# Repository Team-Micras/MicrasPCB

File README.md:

# MicrasPCB

The Micras micromouse PCBs, designed as code: circuits in [Zener](https://docs.pcb.new) (the
Diode `pcb` toolchain), layout in KiCad 10, and every check, fab output and review file built by
CI.

| Board | Status |
|---|---|
| `encoder`: AS5047U wheel encoder daughterboard, 2 layers, 0.79 mm | the previous revision's placement and routing, plus pull resistors on the sensor's SPI inputs; passes every check ([open items](boards/encoder/layout/README.md#open-items)) |
| `wall`: wall-sensor daughterboard (SFH 4550 over a TPS601A, upright, with the emitter's resistor and its AC-coupled selector, joined to the main board by a 2x3 1.27 mm header straddling its bottom edge), one per sensor, 2 layers, 0.79 mm, a paddle 16.0 mm high: 4.2 mm handle, 8.4 mm blade; JLCPCB fits the SMD parts on a 4-up panel, the sensor and header are hand-soldered | placed and routed, passes every check; the main board's wall joints W1-W4 take four ([open items](boards/wall/layout/README.md#open-items)) |
| `main`: STM32H725 controller, 4S power, DRV8874 wheel bridges with INA241 current sensing, fan driver, sensors, ESP32-C5 dual-band radio and debug probe, no USB receptacle (bare pads on the C5's native USB) ([research/next-revision](research/next-revision/README.md)), 4 layers, 1.04 mm, 91.15 x 50 mm | placed and routed for the six-pin wall slots, the fan ring, the ESP32 flashing pads and USB pads: every connection routed, passes every check ([open items](boards/main/layout/README.md#open-items)) |

The v1 main board and its HM-19 Bluetooth module, which plugged into the v1 board's USB-C port,
are at the tag `v1` (e34fb9a).

## How it fits together

```text
spec/<board>.toml ──────────────┐ outline, tab, spec-placed parts      ┌─> build/<board>/<board>_mech.json
                                 v                                      │   (MicrasHardware, micras-simulation)
boards/<board>/<board>.zen ──> pcb apply ──> micras-pcb sch ──> layout/<board>.kicad_sch
components/**/*.zen             (Zener)          ^                layout/<board>.kicad_pcb <─┘ placement + routing in KiCad
boards/<board>/schematic/*.toml ─────────────────┘ schematic placement
                                                     │
          make check: build · warnings · tests · sync · spec · sch · ERC · LVS · previous · DRC · DFM · pytest · parts
                                                     │
          make review: renders · schematic · layers · 3D · assembly · BOM · fab zip ──>  CI artifact
```

- **Zener owns the circuit.** Parts, nets, values, stackup and design rules are code, with
  datasheet evidence in docstrings and `pcb test` test benches for the datasheet requirements.
  `pcb apply` writes the KiCad schematic and syncs the netlist into the layout, keeping hand
  placement and routing (sync is idempotent: a regeneration of an unchanged design is
  byte-identical).
- **`boards/<board>/schematic/` owns how the schematic is drawn.** `pcb apply` writes each sheet
  afresh; `micras-pcb sch` then places it from one file per sheet: where each part goes and how it
  turns, which pins are wired together, the titled frame of each function block, the paper size
  and the order of each module's sheet pins. It redraws every connection with the labels and
  power symbols pcb chose and fails unless KiCad's netlist of the placed schematic equals pcb's,
  so the drawing can never change the circuit. A part without an entry is drafted from the
  netlist by the same rules a person follows (blocks by connectivity, decoupling at the supply
  pin, pulls at their pins, repeated blocks alike, the smallest paper), steered by an optional
  `SCHEMATIC_HINTS` dict in the Zener module that pcb ignores; `micras-pcb sch --draft` writes the
  drafts into the file to adopt and adjust. The `micras-pcb` skill has the file format, the rules
  and the hints.
- **`spec/` owns the mechanics.** `micras-pcb mech` writes the origin and the locked position of
  mechanically critical parts (the encoder's sensor and tab, the wall board's sensor and header,
  the main board's screw holes, battery switch, ESP32 module and wall sensors) into the
  `.kicad_pcb`, and exports the board for the other repos. The main board's and the wall board's
  Edge.Cuts outlines are the spec's (`micras-pcb mech` draws them: the main board's nose, wheel
  notches, encoder slots, fan hole, antenna and switch notches; the wall board's bottom edge,
  sides and corners), and so is the main board's silkscreen of the fan ring and the drive
  blocks' outlines; the encoder's is layout
  geometry (it keeps its previous revision's), and the spec checks its interface features (tab,
  shoulder, tapers and extents). CI fails if the layout drifts.
- **KiCad owns placement and routing**, which stay human-led.
- **`parts/jlc.toml` owns sourcing**: MPN to LCSC number, basic/extended, placement rotation.
- **The order options** come from where each is decided: finish and colours from the Zener
  stackup, the via class and the assembly service from `spec/<board>.toml` `[pcb]` (a test holds
  the via class to the layout's smallest via), and a board under JLCPCB's 10 x 10 mm assembly
  minimum is ordered as the panel its spec's `[panel]` describes (KiKit, `make fab`). Every board is
  leaded HASL. JLCPCB prints no paste on the parts the team solders itself (`assembly = "hand"`):
  their paste goes to a separate stencil file (`micras-pcb` skill, JLCPCB outputs).

### Why Zener and KiCad

- **KiCad 10 is the contract between tools.** `kicad-cli` runs ERC, DRC and every export
  headless, MicrasHardware imports the board through KiCad's STEP, and JLCPCB's assembly flow is
  built around KiCad. The committed KiCad project is a complete design on its own: without Zener,
  the boards continue in plain KiCad and only the schematic stage changes.
- **Zener writes the schematic**, the part of KiCad that is weakest as code: KiCad 10 has no
  headless schematic API, and its verbose files are a poor target for language models. Zener emits
  a real KiCad schematic to review, syncs the netlist into the layout without touching hand
  placement and routing, type-checks power nets, runs datasheet test benches, and is built to be
  written by agents (its skills are in `.claude/skills/`).
- **`tools/micras_pcb` covers the rest**: the spec-driven outline and mech export, LVS, the rule
  checks, and the JLCPCB package with its rotation offsets.

### Known limits

- **Zener is pre-1.0 and changes fast**; commands get renamed or removed between releases. The
  toolchain is pinned in `versions.env` and bumped in its own PR, where CI shows what regenerates.
- **Zener has no LCSC picker, and its JLC placement export applies no rotation corrections.**
  `parts/jlc.toml` carries the LCSC number and a per-part rotation offset, and `make fab` builds
  the JLCPCB BOM and CPL from it. JLCPCB's placement preview is the final word on each part's
  rotation (`rotation_verified`).
- **Zener labels the nets between module sheets twice**: the main board's schematic has one
  sheet per Zener module (`Project(..., layout = False)`), and pcb 0.4.81 puts
  a global label beside each sheet pin and hierarchical label
  ([diodeinc/pcb#1520](https://github.com/diodeinc/pcb/issues/1520)), so KiCad's ERC warns
  `same_local_global_label` and `multiple_net_names` on those nets. The placement keeps the global
  label at the pin and draws the hierarchical one in the sheet's ports column, wired to a copy of
  the global one (`micras-pcb sch`). Each board's
  `erc.toml` accepts these two warnings with that reason, and only them; they go away with a pcb
  release that includes [diodeinc/pcb#1522](https://github.com/diodeinc/pcb/pull/1522)
  ([known faults](boards/main/layout/README.md#known-faults)).
- **KiCad 10 has no headless layout API**: the IPC API needs a running KiCad, and the SWIG
  `pcbnew` module is deprecated and goes away in KiCad 11. The tools use `kicad-cli` and edit the
  `.kicad_pcb` s-expressions directly (`tools/micras_pcb/sexpr.py`).
- **Git cannot merge a `.kicad_pcb` safely** (KiCad 10 has no merge driver): one person edits a
  board's layout at a time.
- **Footprints from EasyEDA/LCSC have documented errors** (reversed polarity, wrong pin numbering,
  mismatched pads). Use KiCad library footprints where they exist, and check every footprint
  against the datasheet land pattern, its 3D model and JLCPCB's preview.
- **JLCPCB has no ordering API open to small teams**: order by uploading `build/<board>/fab/` by
  hand.

## Setup (Linux / WSL2)

```sh
./ci/install-kicad.sh                                                                # KiCad 10 from the PPA, see versions.env
curl -fsSL https://raw.githubusercontent.com/diodeinc/pcb/main/install.sh | bash      # Zener toolchain launcher
make setup                                                                            # uv env + pinned pcb toolchain + KiKit
```

Optional: the [Zener VS Code extension](https://docs.pcb.new/pages/vscode) shows a live
schematic preview of `.zen` files.

## Everyday commands

```sh
make gen        # regenerate KiCad files from the sources (run after every source change)
make check      # every gate CI runs, with a pass/FAIL summary
make review     # build/<board>/review and fab: schematic PDF, layer SVGs, renders, GLB/STEP, fab package,
                #   and build/main/review/assembly.*: the main board with its wall and encoder boards in place
make fab        # build/<board>/fab: JLCPCB gerbers zip (no paste on hand-soldered parts), BOM, CPL, order options
                #   (the wall board's as a 4-up panel) and the team's stencil for the hand-soldered parts
pcb open boards/encoder/encoder.zen     # open the layout in KiCad
make parts-online   # JLCPCB stock and basic/extended status (run before ordering)
make quote          # JLCPCB's bare-board price with each board's finish, colours and via class
```

`make check` runs every gate below, even after one fails, then prints a pass/FAIL line per gate
and fails if any gate failed.

| Gate | Tool | Catches |
|---|---|---|
| build | `pcb` | Zener errors, electrical type checks (power pins), formatting, dependency drift |
| warnings | `pcb build -D warnings` | a build warning: a net outside a part's declared operating range, a capacitor rated below its net |
| test | `pcb test` | datasheet requirements: per component (`components/**/test/`) and per board (`boards/<board>/test/`: application circuits, values computed with the datasheet equations) |
| layout-check | `pcb layout --check`, `micras-pcb rules/mech --check` | layout no longer matches the netlist, rules or spec drift |
| sch | `micras-pcb sch --check` | a placement entry, wire or hint naming what its sheet does not have, a sheet symbol too small for its pins, overlaps or items off the page, a placed sheet out of date with the sources; prints how many parts each sheet drafts |
| ERC | `kicad-cli sch erc` | schematic electrical rules; `boards/<board>/erc.toml` names the nets supplied from off the board (the PWR_FLAG role) and the warnings a board accepts, rule by rule with the reason |
| LVS | `micras-pcb lvs` | schematic and PCB connect different pads |
| previous | `micras-pcb previous compare <board>` | a replicated board (the encoder) connects or names anything differently from its previous revision, except the changes in `boards/<board>/changes.toml` |
| DRC | `kicad-cli pcb drc` + `rules/jlcpcb.kicad_dru` | JLCPCB clearances (copper, SMD pad to pad, hole to track), widths, drills, edge distances |
| DFM | `pcb dfm` + `rules/jlcpcb-pdk.toml` | geometry-level manufacturability (Diode's sourced JLCPCB PDK) |
| pytest | `pytest` | board contracts (encoder joint, firmware pin map), the assembly (each wall and encoder board standing where the specs put it, its pads on its joint's, clear of the main board and its parts), the fab package (every assembled board or its panel at least 10 x 10 mm, the panel's outlines, tabs and CPL, each board's via class), power tree, every schematic item on its sheet's page, no overlapping texts, bodies or wires on a sheet, every board's schematic drafted whole from its Zener source (pcb's netlist, nothing overlapping), decoupling at the pin, encoder slot fit, routing style (every track straight at a multiple of 45 degrees, no arcs, no acute corners), courtyards, paste, 3D models, part data |
| lint | `ruff` | Python lint and format |
| parts | `micras-pcb parts` | a part without an LCSC mapping |

Every board passes every gate once laid out. A schematic-only board (its root declares `Project(layout = False)`, so it has no
`.kicad_pcb`) passes the schematic gates, and LVS, DRC, DFM, the layout tests and the gerber, CPL
and 3D outputs skip it with that reason; `make fab` writes
its BOM alone. The main board's README ([known faults](boards/main/layout/README.md#known-faults))
gives the root cause of each warning that remains.

## CI

- `.github/workflows/ci.yml`: on every push and PR, installs the pinned KiCad and Zener,
  checks that `make gen` changes nothing, runs `make check`, builds the review outputs and fab package
  (uploaded as the run's artifact).
- GitHub Actions, the Python dev tools (`uv.lock`), KiCad and Zener (`versions.env`) are bumped
  by hand; a KiCad or Zener bump can change the generated files.
- JLCPCB stock is not checked in CI (it changes daily and the API is undocumented): run
  `make parts-online` before ordering.

To look at a board, download the run's artifact, or open the project in KiCad
(`pcb open boards/<board>/<board>.zen`). The boards are also viewed online in a self-hosted
[KiCad Prism](https://github.com/krishna-swaroop/KiCAD-Prism), which takes each board's layout
folder as a project and shows the board's README from it (`boards/<board>/layout/README.md`).
Each layout folder's `.prism.json` names the root schematic and the board, so Prism does not take
the first sheet in the folder (main's `DRIVERS.kicad_sch`) as the root and drop it from the viewer.
Prism shows one board at a time; the robot's boards together are in the run's artifact:
`build/main/review/assembly.glb` and `assembly.step` (the main board with the four wall boards and
both encoder boards standing in their joints, origin at the robot's) and the renders
`assembly-iso-left.png`, `assembly-iso-right.png` (from the front-left and front-right) and
`assembly-top.png`. `micras-pcb assembly` places each daughterboard from the specs on a build copy
of the main board, as a 3D model on its joint footprint, and fails if KiCad's export puts it
anywhere else.

## Working with Claude Code

`CLAUDE.md` holds the agent rules. `.claude/settings.json` adds two hooks: one rebuilds any
`.zen` file the agent edits and feeds errors back immediately; the other blocks text edits to
generated or KiCad-owned files. `.claude/skills/` holds the `micras-pcb` workflow skill (parts,
JLCPCB outputs, KiCad scripting, review gates) and Diode's Zener skills (language, component
librarian, SPICE). Agents write code and deterministic tools grade it; people own footprint and
pin-1 checks, placement and routing, and the fab order.

## Repository

```text
boards/<board>/        <board>.zen, pcb.toml, layout/ (KiCad project: .kicad_pcb is KiCad-owned, README.md is
                       the board's description, .prism.json the root files for KiCad Prism, the rest generated)
boards/<board>/schematic/  one placement file per schematic sheet (micras-pcb sch): parts, wires, frames, paper;
                       drafted entries marked auto = true
boards/<board>/previous/  snapshot of the board's previous revision (board.json) for the connectivity comparison,
                       and the script that builds its layout from that revision (transfer_layout.py): the encoder
boards/main/layout/*.py  the main board's placement, routing and silkscreen scripts (place.py, route.py, silk.py;
                       its layout README says what each does) and their 45-degree grid router (router.py)
boards/main/firmware.toml  the firmware's pin map and drive settings (from MicrasFirmware), tested against the board
boards/main/firmware_changes.toml  the firmware changes the board needs, applied on top of firmware.toml in the tests
boards/<board>/test/   Zener test benches of the board's circuit
components/<mfr>/<P>/  reusable Zener packages: symbol, footprint (STEP embedded), .zen, test bench, README
spec/                  mechanical single source of truth per board; main_chassis.json, the chassis's shadow over the
                       main board from MicrasHardware's model (tools/chassis_shadow.py, run in that repo's environment)
parts/jlc.toml         MPN -> LCSC mapping
rules/                 JLCPCB KiCad DRC rules, DFM PDK, KiCad rule severities
tools/micras_pcb/      Python glue: mech, lvs, checks, jlc, panel, order, outputs, assembly, previous, firmware, layout,
                       schematic placement and drafts (`uv run micras-pcb --help`)
tests/                 pytest design tests
research/next-revision/ the main board's design research (entered as boards/main) and its calculation scripts
ci/                    KiCad, toolchain and KiKit install, for CI and local setup
versions.env           pinned KiCad, Zener, Freerouting and KiKit versions
```

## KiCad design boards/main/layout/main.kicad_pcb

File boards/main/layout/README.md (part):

# Main board

The Micras main board: the STM32H725RGV6 controller, a 4S
battery input with its fuse, VSYS behind a Schottky, separate digital and analog 3.3 V rails, two
DRV8874 wheel bridges with in-line INA241 current sensing, the STSPIN958 fan driver, the IMU,
the joints for four wall-sensor boards (boards/wall) on a shared emitter current sink, the slots
for the two encoder boards, the
ESP32-C5 dual-band radio, debug probe and data link with its flashing pads and bare USB pads, and
the user interface. The board has no USB receptacle: bare pads J3 take a USB cable's data pair and
ground, soldered once, on the ESP32-C5's native USB; a programmer's 5 V pin on the flashing pads or
the SWD pads (5V_IN) powers it for flashing without the pack.

The design is [research/next-revision/README.md](../../../research/next-revision/README.md): its
design basis (maxon DCX 10 L 4.5 V motors on a 4S pack, no boost; no USB receptacle; no 5 V rail), the options it recommends, and its connection lists A.1-A.6. The blocks it keeps are
the v1 main board's (MicrasPCB e34fb9a, `boards/main`), with their designators; new parts continue each series (C80-C114, D14-D15, D17,
IC8-IC9, J2-J3, L4-L6, Q9, R58-R97, U8-U13), and the designators of removed parts are not reused.

The board is 91.15 x 50 mm (x 47.6 to -43.55 in the robot frame), 4 layers, 1.04 mm, every part on the
top side. Its mechanics are [`spec/main.toml`](../../../spec/main.toml): the outline, the screw
holes, the encoder slots, the wall joints, the fan hole and its low-part ring, the antenna and switch
notches, the parts that mate with the robot or the outline (IC1 among them) and the zones the chassis
takes over the board (see [Layout](#layout)). The robot fills the smallest turning circle the parts
allow, 49.46 mm round the axle: the nose (its front edge 18.2 mm wide between 4 mm corner arcs, with long chamfers meeting the sides in 4 mm shoulder arcs) holds the diagonal
wall sensors at the front, IC1 behind them turned 45 deg and partly over the fan ring (spec `[ic1]`:
x 32.35, its courtyard 0.73 mm from the fan hole and 1.82 mm from the diagonal joints' courtyards, for its
decoupling; the ring's silk breaks at its pads), and the frontal sensors beside it at y +-19.8; the parts ahead
of the fan hole's centre keep about the committed board's density (39.1 %, 34.5 % on the committed
outline). The rear edge sits where U13's antenna corner reaches the same circle; the module alone
would allow a rear edge up to -41.3 (its courtyard behind the right drive block's rear screw boss).
The front-row LEDs (D1, D2, D4/R4, D5/R5) move back 5.9 mm with the front edge, in the same
arrangement (owner, 2026-11-03).

## Files

The board files are in `boards/main/` (this README sits in its `layout/` folder).

| File | Sheet instance | Contents |
|---|---|---|
| [`main.zen`](../main.zen) | root | IC1 (STM32H725RGV6) and its supply network (C1-C17, L1, R67), the ST-Link pads SWD1 (NRST on pad 1, 5V_IN on pad 5), M2 screw holes H1-H4 |
| [`Regulators.zen`](../Regulators.zen) | `REGULATORS` | J1 battery connector with its fuse F1 and TVS D15, battery switch SW4/Q6, battery measurement R44/R45, VSYS diodes D14 (from VBAT) and D17 (from 5V_IN), 3V3_D buck IC7, 3V3_A LDO U8 |
| [`Drivers.zen`](../Drivers.zen) | `DRIVERS` | IC8/IC9 (DRV8874) bridges for M2/M1 with their 10 mOhm shunts R65/R75 and 47 uH chokes L4/L5, IC6 (STSPIN958) fan driver for M3 with its shunt R31 and 4.7 uH choke L6 |
| [`Sensors.zen`](../Sensors.zen) | `SENSORS` | IC2 (LSM6DSV) IMU, U10/U11 (INA241A2) current amplifiers, wall joints W1-W4 (the wall boards' 2x3 joints: receiver output, GND, 3V3_A, 3V3_D, sink, PWM) with the receivers' 1 kOhm loads R14/R18/R22/R26, the emitter current sink U12/Q9/R83 with its DAC set-point, encoder slots EC1/EC2 |
| [`Peripherals.zen`](../Peripherals.zen) | `PERIPHERALS` | SW1 DIP switch, SW2/SW3 buttons, R42 BOOT0 pull-down, BZ1 buzzer, D1/D2 (CT-1515UGRBC) status LEDs, D4/D5 LEDs |
| [`Esp.zen`](../Esp.zen) | `ESP` | U13 (ESP32-C5-MINI-1-N4) with its decoupling, EN RC, GPIO28 pull-up, flashing pads J2 (`components/micras/EspProgPads`, 5V_IN on pad 2), the USB pads J3 (`components/micras/UsbPads`, GPIO13 D-, GPIO14 D+), and the links to the MCU with their series resistors R86, R88, R95, R96 and the ESP_CSn pull-up R97 |
| [`passives.zen`](../passives.zen) | | value, package, rating and part number of every resistor, ceramic capacitor and LED line |
| [`schematic/`](../schematic) | | how each sheet is drawn (`micras-pcb sch`): the root with IC1, its supply domains, the SWD header and the module sheets, and one file per module sheet, each block in a titled frame |
| [`erc.toml`](../erc.toml) | | nets supplied from off the board (BAT_P, GND, GND_BAT, 5V_IN) or through a passive part (VBAT, VSYS, 3V3_D, the LDO input, VDDA), the PWR_FLAG role for ERC; the two ERC warnings the module sheets leave until a pcb release includes [diodeinc/pcb#1522](https://github.com/diodeinc/pcb/pull/1522) (see [Known faults](#known-faults)) |
| [`firmware_changes.toml`](../firmware_changes.toml) | | the firmware changes this board needs against the v1 firmware (see [Firmware changes](#firmware-changes)) |
| [`test/`](../test) | | `pcb test` benches: MCU and ESP links, power, drivers, peripherals |
| [`layout/`](.) | | this folder: the KiCad project; `main.kicad_sch` is the root sheet, with one sheet per module (`REGULATORS.kicad_sch`, ...); the `.kicad_pcb` holds placement and routing; `place.py` places every part, `route.py` pours the planes and routes the board and `silk.py` places the reference designators (see [Layout](#layout)) |
| [`spec/main.toml`](../../../spec/main.toml) | | mechanical interface: thickness, axle origin, outline, screw holes, encoder slots, wall joints, fan hole and fan ring, wheel, antenna and switch notches, the ESP32 module's, battery switch's and wall joints' positions, the chassis zones, the silkscreen it draws (fan ring, drive blocks); the via-in-pad order option |

Each module is its own sheet of the KiCad schematic (`Project(..., layout=False)` in its `.zen`),
its signal ports named after the nets they carry where those names are identifiers, as on the
v1 main board. `SENSORS` takes the shared SPI bus once (`SPI_SCK`, `SPI_MISO`, `SPI_MOSI`) with
each device's chip select, not one `Spi` port per device, so it has 26 sheet pins instead of 32:
pcb 0.4.81 places the sheet symbols on the root one by one in the order of their names, each as
near the page centre as the earlier ones leave room, by their boxes alone, and the 32-pin symbol
fits only against the page's left edge, where its pin labels run past the page. At 26 pins it sits
right of `ESP`, and `tests/test_schematic.py` checks that every label stays on its page. Each sheet's docstring describes its circuit with the datasheet figure, table or
equation behind each value; [`tests/test_main.py`](../../../tests/test_main.py) checks the power tree, the analog
rail, the decoupling and the firmware contract on the generated netlist.

## Power

```text
4S LiPo 12.0-16.8 V (17.4 V HV) ─ J1 ─ BAT_P ─ F1 12 A fuse ─ VBAT (D15 SMAJ18A to GND_BAT)
   pack - ─ GND_BAT ─ Q6 HSBB3072 (SW4, slew-limited) ─ GND
VBAT ─┬─ IC8/IC9 DRV8874 VM, IC6 STSPIN958 VS
      ├─ R44/R45 20k/2k ─ PC5 (Battery_Voltage, ratio 11.0)
      └─ D14 B5819W ─ VSYS 11.4-17.4 V (3.8-5.0 V on 5V_IN alone)
5V_IN (a programmer's 5 V pin: J2 pad 2, SWD1 pad 5) ─ D17 B5819W ─ VSYS
      VSYS ─┬─ IC7 L6981C33 ─ 3V3_D: MCU VDD, ESP32, IMU, encoders, LEDs, emitters
            └─ R58 22 Ω + C80 10 µF ─ U8 ADP7142 3.3 V (EN = 3V3_D) ─ 3V3_A: VDDA (R67 0 Ω),
                  INA241 VS/REF1, phototransistor collectors, emitter-sink op-amp and its bias
```

- **VSYS** is VBAT behind D14, or 5V_IN behind D17, and feeds only the two regulators. D14 keeps
  5V_IN off VBAT, the bridges' bulk and the pack; D17 keeps the pack off the programmer.
- **No USB supply input**: every rail comes from J1 but for flashing. 5V_IN takes a USB-serial
  adapter's, a clone ST-Link's or the J3 USB cable's 5 V wire (never a 3.3 V one) on J2 pad 2 or SWD1 pad 5 and runs the 3V3 rails
  without the pack: 0.19-0.25 A while flashing, VSYS 3.8 V or more, where the buck still
  regulates; the bridges and the fan stay unpowered and VBAT reads near 0 V (Regulators.zen,
  VSYS). On the bench, a current-limited supply at 12-16.8 V goes into J1 (a lead with the pack's
  JST PA plug) with SW4 on; with the motors and the fan disabled, set the limit just above what
  the 3V3 rails draw.
- **3V3_D**: the L6981C33 buck, as on the v1 main board, now from VSYS; every capacitor on 3V3_D,
  the ESP32's 22 uF included, stays inside its 30.5-145 uF compensation window.
- **3V3_A**: the ADP7142ACPZN3.3 LDO from VSYS through 22 Ohm + 10 uF 1210, its EN on 3V3_D so VDDA
  never leads VDD; about 10 mA typical, 23 mA worst case, 0.32 W at the HV pack's top.
- **No 5 V rail** (5V_IN is a programming input, not a rail).
- **Battery voltage**: R44/R45 20k/2k into PC5 with C59 100 nF: 1.58 V at 17.4 V and 2.20 V at
  D15's 24.2 V clamp, under PC5's 4.0 V absolute maximum (a ratio of 6 reaches 4.03-4.10 V there).
- **Fuse**: F1, Littelfuse 0501012.WR1 (12 A fast-acting, 32 VDC, 150 A interrupting, 3.2 mOhm;
  a 1206 under the chassis's 1.5 mm zone), carries the whole battery current from J1 to VBAT: a
  short on the board opens it. It carries the 4 A rms budget with 2x margin at 75 C (8.2 A) and
  holds the 10.1 A summed peak limits at 75 C (10.2 A); it clears a 40 A partial fault in about
  6 s (the 20 A row: about 25 s). Turning the board on is under 0.01 A2s against its 20.3 A2s.
- **Battery switch**: Q6 as on the v1 main board, its gate fed from VBAT through SW4; C58 100 nF
  gate-source and C114 1 nF gate-drain keep it off when the pack is plugged in (the board then
  sees no edge), and slew VBAT at about 0.06 V/us when SW4 closes, under the STSPIN958's
  0.5 V/us. SW4 is the SK-12D29-G060
  (DC 24 V, the v1 main board's switch body with a 6.0 mm lever, its own footprint). The connector
  keys the polarity; a reversed pack forward-biases D15 through F1, which opens.
- **TVS**: D15 (SMAJ18A, 18 V standoff, 20-22.1 V breakdown) behind F1, VBAT to GND_BAT, so a
  TVS that fails short opens the fuse. With the
  pack pulled while the bridges brake, it holds VBAT near 21-23 V through Q6's channel (SW4 on) or
  its body diode (SW4 off), at most 24.2 V, below every rating on VBAT and VSYS (50 V MLCCs,
  Q6's 30 V, the DRV8874's 40 V).
- **No electrolytics**: VBAT carries only ceramics, every 10 uF a 50 V X7R 1210 (61 uF effective
  at 16.8 V); the research's
  [VBAT capacitance](../../../research/next-revision/README.md#power-tree) compares the options and
  quantifies the VBAT overvoltage cases.

## Drivetrain and current sensing

- **Bridges**: one DRV8874PWPR per motor, PH/EN mode (PMODE = GND), PWM on EN and direction on
  PH (right PA10/PB6, left PC6/PA12), IMODE = GND (fixed off-time, automatic retry), ITRIP 2.97 A
  from RIPROPI 2.0 kOhm and VREF 2.67 V (4.7k/20k from 3V3_D). nSLEEP of both on Motors_Enable
  (PB7) with R49 100 kOhm to GND; nFAULT of both wire-ORed on Motors_nFault (PD2) with R60
  10 kOhm to 3V3_D. Per bridge: 100 nF + 4 x 10 uF 50 V X7R 1210 on VM, 100 nF VCP, 22 nF
  CPH-CPL.
- **Motor path**: OUT1 -> 10 mOhm WSK2512 4-terminal shunt -> 47 uH MTQH707050S470M choke -> motor
  connector; OUT2 -> connector.
- **Current**: INA241A2 (gain 20) on each shunt, VS and REF1 on 3V3_A, REF2 on GND: 0.2 V/A
  around VDDA / 2, +7.25 / -8.15 A at 3V3_A 3.3 V, into PA6 (left, a fast ADC channel) and PC1 (right)
  through 150 Ohm (R78/R79, R_iso), with 1 nF X7R on the ADC line (C102 3.5 mm from PC1, C105
  1.9 mm from PA6, 2 mm of track from the pin); the firmware samples them
  for at least 0.7 us, so the ADC's kickback from a wall-sensor conversion settles below 1 mA.

## Fan

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
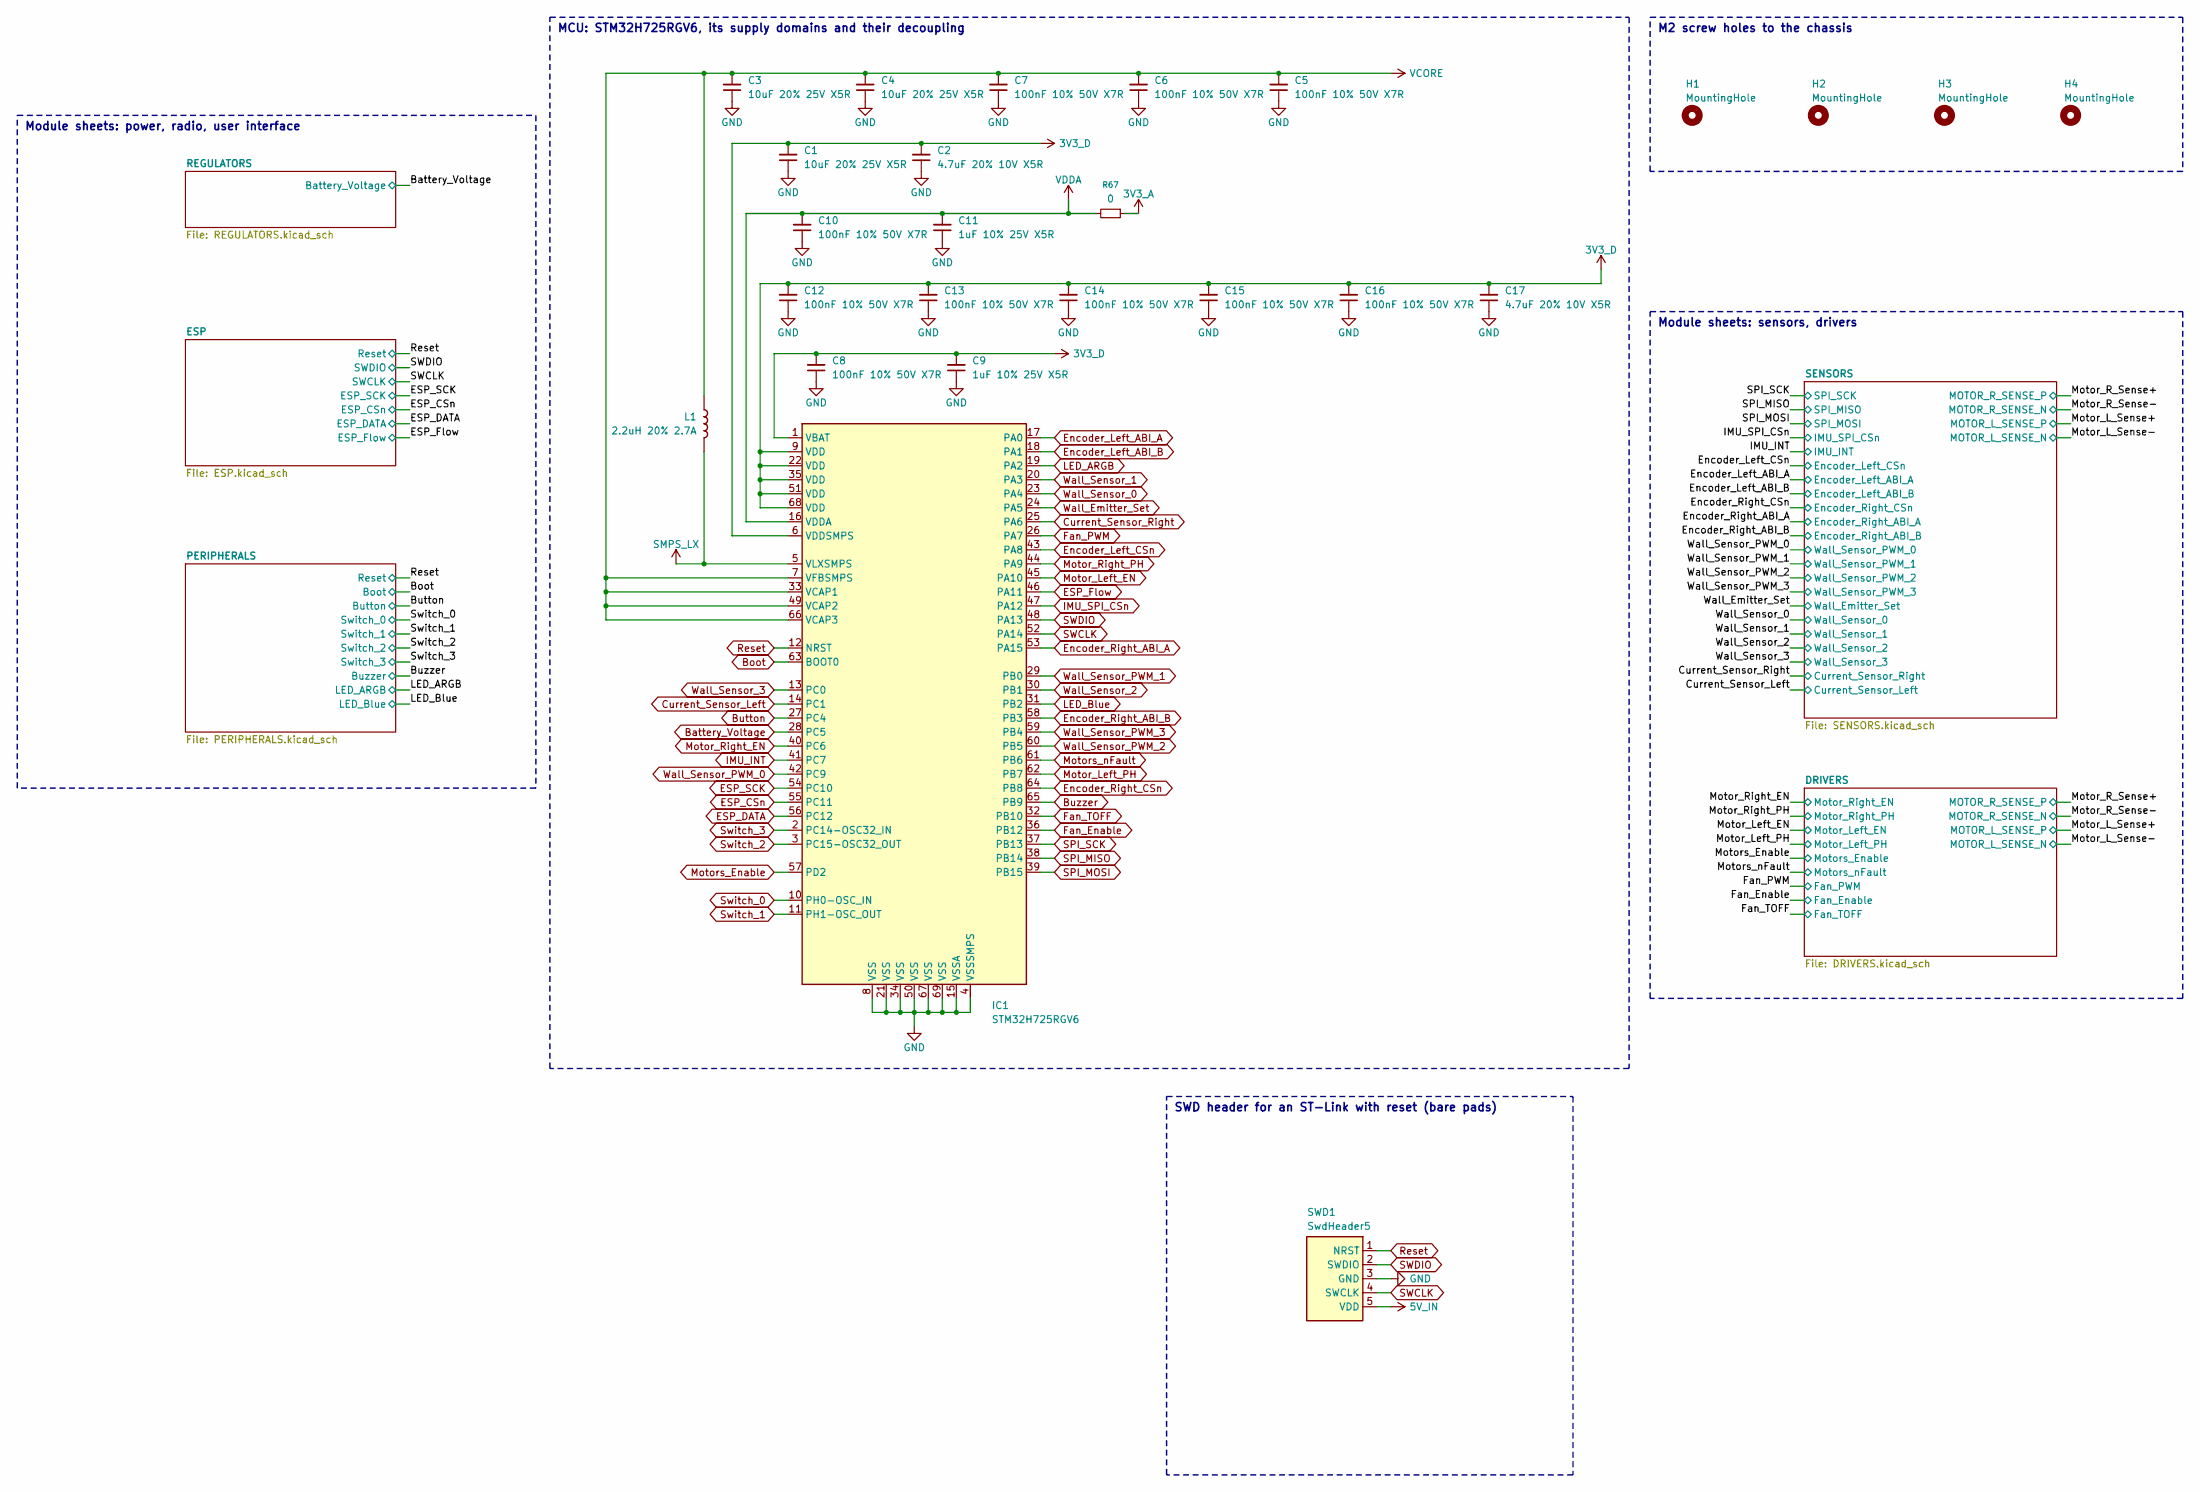
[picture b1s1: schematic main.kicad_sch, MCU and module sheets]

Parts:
C1, C3, C4: 10uF 20% 25V X5R; C_0603_1608Metric
C2, C17: 4.7uF 20% 10V X5R; C_0402_1005Metric
C5, C6, C7, C8, C10, C12, C13, C14, C15, C16: 100nF 10% 50V X7R; C_0402_1005Metric
C9, C11: 1uF 10% 25V X5R; C_0402_1005Metric
H1, H2, H3, H4: MountingHole; MountingHole_2.4mm_NPTH
IC1: STM32H725RGV6; QFN-68-1EP_8x8mm_P0.4mm_EP6.5x6.5mm_SplitPaste
L1: 2.2uH 20% 2.7A; IND-SMD_L2.0-W1.6-B
R67: 0; R_0402_1005Metric
SWD1: SwdHeader5; PinHeader_1x05_P1.27mm_Vertical

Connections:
3V3_A: R67.1; also elsewhere on the board
3V3_D: C1.2, C2.2, C8.2, C9.2, C12.2, C13.2, C14.2, C15.2, C16.2, C17.2, IC1.1 (VBAT), IC1.6 (VDDSMPS), IC1.9 (VDD), IC1.22 (VDD), IC1.35 (VDD), IC1.51 (VDD), IC1.68 (VDD); also elsewhere on the board
5V_IN: SWD1.5 (VDD); also elsewhere on the board
Battery_Voltage: IC1.28 (PC5); also elsewhere on the board
Boot: IC1.63 (BOOT0); also elsewhere on the board
Button: IC1.27 (PC4); also elsewhere on the board
Buzzer: IC1.65 (PB9); also elsewhere on the board
Current_Sensor_Left: IC1.14 (PC1); also elsewhere on the board
Current_Sensor_Right: IC1.25 (PA6); also elsewhere on the board
ESP_CSn: IC1.55 (PC11); also elsewhere on the board
ESP_DATA: IC1.56 (PC12); also elsewhere on the board
ESP_Flow: IC1.46 (PA11); also elsewhere on the board
ESP_SCK: IC1.54 (PC10); also elsewhere on the board
Encoder_Left_ABI_A: IC1.17 (PA0); also elsewhere on the board
Encoder_Left_ABI_B: IC1.18 (PA1); also elsewhere on the board
Encoder_Left_CSn: IC1.43 (PA8); also elsewhere on the board
Encoder_Right_ABI_A: IC1.53 (PA15); also elsewhere on the board
Encoder_Right_ABI_B: IC1.58 (PB3); also elsewhere on the board
Encoder_Right_CSn: IC1.64 (PB8); also elsewhere on the board
Fan_Enable: IC1.36 (PB12); also elsewhere on the board
Fan_PWM: IC1.26 (PA7); also elsewhere on the board
Fan_TOFF: IC1.32 (PB10); also elsewhere on the board
GND: C1.1, C2.1, C3.1, C4.1, C5.1, C6.1, C7.1, C8.1, C9.1, C10.1, C11.1, C12.1, C13.1, C14.1, C15.1, C16.1, C17.1, IC1.4 (VSSSMPS), IC1.8 (VSS), IC1.15 (VSSA), IC1.21 (VSS), IC1.34 (VSS), IC1.50 (VSS), IC1.67 (VSS), IC1.69 (VSS), SWD1.3 (GND); also elsewhere on the board
IMU_INT: IC1.41 (PC7); also elsewhere on the board
IMU_SPI_CSn: IC1.47 (PA12); also elsewhere on the board
LED_ARGB: IC1.19 (PA2); also elsewhere on the board
LED_Blue: IC1.31 (PB2); also elsewhere on the board
Motor_Left_EN: IC1.45 (PA10); also elsewhere on the board
Motor_Left_PH: IC1.62 (PB7); also elsewhere on the board
Motor_Right_EN: IC1.40 (PC6); also elsewhere on the board
Motor_Right_PH: IC1.44 (PA9); also elsewhere on the board
Motors_Enable: IC1.57 (PD2); also elsewhere on the board
Motors_nFault: IC1.61 (PB6); also elsewhere on the board
Reset: IC1.12 (NRST), SWD1.1 (NRST); also elsewhere on the board
SMPS_LX: IC1.5 (VLXSMPS), L1.2
SPI_MISO: IC1.38 (PB14); also elsewhere on the board
SPI_MOSI: IC1.39 (PB15); also elsewhere on the board
SPI_SCK: IC1.37 (PB13); also elsewhere on the board
SWCLK: IC1.52 (PA14), SWD1.4 (SWCLK); also elsewhere on the board
SWDIO: IC1.48 (PA13), SWD1.2 (SWDIO); also elsewhere on the board
Switch_0: IC1.10 (PH0-OSC_IN); also elsewhere on the board
Switch_1: IC1.11 (PH1-OSC_OUT); also elsewhere on the board
Switch_2: IC1.3 (PC15-OSC32_OUT); also elsewhere on the board
Switch_3: IC1.2 (PC14-OSC32_IN); also elsewhere on the board
VCORE: C3.2, C4.2, C5.2, C6.2, C7.2, IC1.7 (VFBSMPS), IC1.33 (VCAP1), IC1.49 (VCAP2), IC1.66 (VCAP3), L1.1
VDDA: C10.2, C11.2, IC1.16 (VDDA), R67.2
Wall_Emitter_Set: IC1.24 (PA5); also elsewhere on the board
Wall_Sensor_0: IC1.23 (PA4); also elsewhere on the board
Wall_Sensor_1: IC1.20 (PA3); also elsewhere on the board
Wall_Sensor_2: IC1.30 (PB1); also elsewhere on the board
Wall_Sensor_3: IC1.13 (PC0); also elsewhere on the board
Wall_Sensor_PWM_0: IC1.42 (PC9); also elsewhere on the board
Wall_Sensor_PWM_1: IC1.29 (PB0); also elsewhere on the board
Wall_Sensor_PWM_2: IC1.60 (PB5); also elsewhere on the board
Wall_Sensor_PWM_3: IC1.59 (PB4); also elsewhere on the board

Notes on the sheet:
MCU: STM32H725RGV6, its supply domains and their decoupling
SWD header for an ST-Link with reset (bare pads)
M2 screw holes to the chassis
Module sheets: power, radio, user interface
Module sheets: sensors, drivers

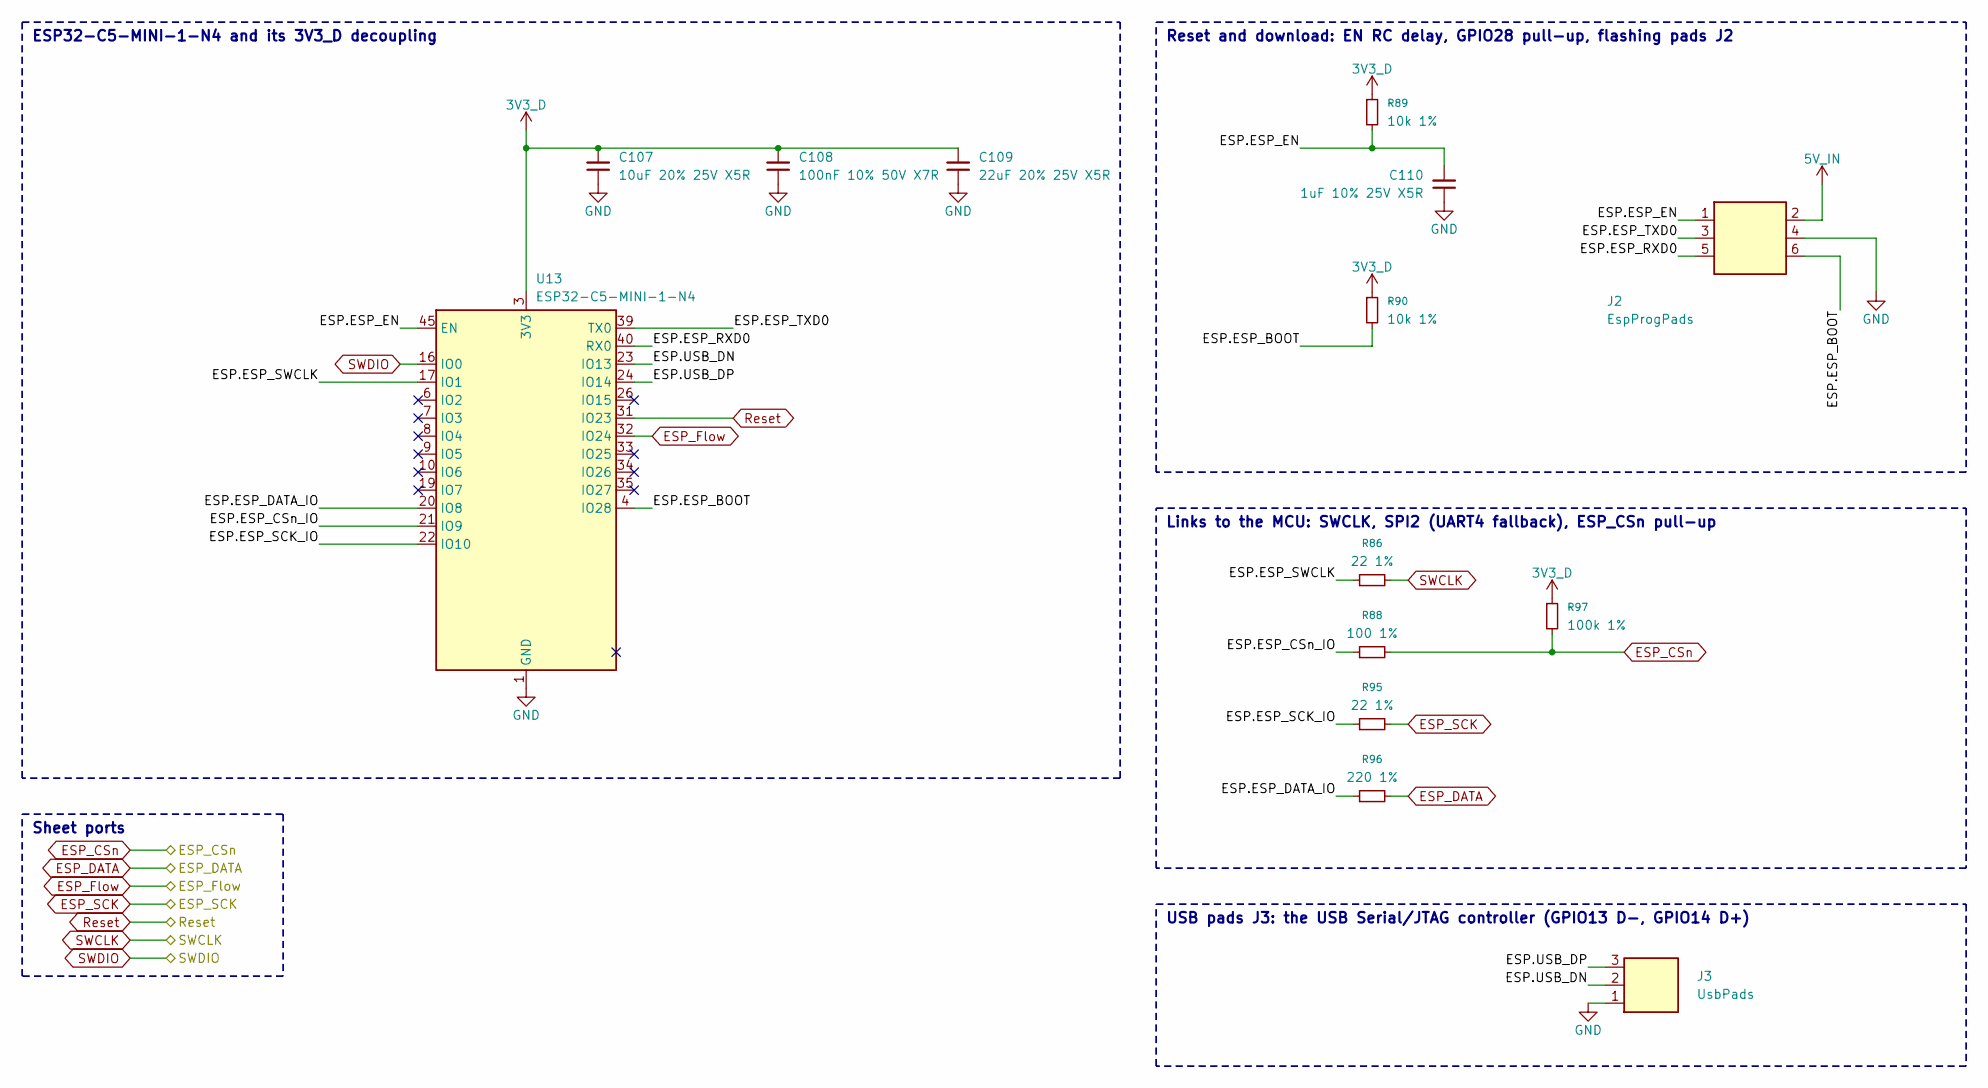
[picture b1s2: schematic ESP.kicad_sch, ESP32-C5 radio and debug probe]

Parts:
C107: 10uF 20% 25V X5R; C_0603_1608Metric
C108: 100nF 10% 50V X7R; C_0402_1005Metric
C109: 22uF 20% 25V X5R; C_0805_2012Metric
C110: 1uF 10% 25V X5R; C_0402_1005Metric
J2: EspProgPads; EspProgPads_2x03_P1.27mm
J3: UsbPads; UsbPads_1x03_P1.27mm
R86, R95: 22 1%; R_0402_1005Metric
R88: 100 1%; R_0402_1005Metric
R89, R90: 10k 1%; R_0402_1005Metric
R96: 220 1%; R_0402_1005Metric
R97: 100k 1%; R_0402_1005Metric
U13: ESP32-C5-MINI-1-N4; ESP32-C5-MINI-1

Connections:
3V3_D: C107.2, C108.2, C109.2, R89.1, R90.1, R97.1, U13.3 (3V3); also elsewhere on the board
5V_IN: J2.2; also elsewhere on the board
ESP.ESP_BOOT: J2.6, R90.2, U13.4 (IO28)
ESP.ESP_CSn_IO: R88.1, U13.21 (IO9)
ESP.ESP_DATA_IO: R96.1, U13.20 (IO8)
ESP.ESP_EN: C110.2, J2.1, R89.2, U13.45 (EN)
ESP.ESP_RXD0: J2.5, U13.40 (RX0)
ESP.ESP_SCK_IO: R95.1, U13.22 (IO10)
ESP.ESP_SWCLK: R86.1, U13.17 (IO1)
ESP.ESP_TXD0: J2.3, U13.39 (TX0)
ESP.U13.NC_ESP32-C5-MINI-1_IO2: U13.6 (IO2)
ESP.U13.NC_ESP32-C5-MINI-1_IO3: U13.7 (IO3)
ESP.U13.NC_ESP32-C5-MINI-1_IO4: U13.8 (IO4)
ESP.U13.NC_ESP32-C5-MINI-1_IO5: U13.9 (IO5)
ESP.U13.NC_ESP32-C5-MINI-1_IO6: U13.10 (IO6)
ESP.U13.NC_ESP32-C5-MINI-1_IO7: U13.19 (IO7)
ESP.U13.NC_ESP32-C5-MINI-1_IO15: U13.26 (IO15)
ESP.U13.NC_ESP32-C5-MINI-1_IO25: U13.33 (IO25)
ESP.U13.NC_ESP32-C5-MINI-1_IO26: U13.34 (IO26)
ESP.U13.NC_ESP32-C5-MINI-1_IO27: U13.35 (IO27)
ESP.USB_DN: J3.2, U13.23 (IO13)
ESP.USB_DP: J3.3, U13.24 (IO14)
ESP_CSn: R88.2, R97.2; also elsewhere on the board
ESP_DATA: R96.2; also elsewhere on the board
ESP_Flow: U13.32 (IO24); also elsewhere on the board
ESP_SCK: R95.2; also elsewhere on the board
GND: C107.1, C108.1, C109.1, C110.1, J2.4, J3.1, U13.1 (GND), U13.2 (GND), U13.42 (GND), U13.43 (GND), U13.46 (GND), U13.47 (GND), U13.48 (GND), U13.50 (GND), U13.51 (GND), U13.52 (GND), U13.53 (GND), U13.54 (GND), U13.55 (GND), U13.56 (GND), U13.57 (GND), U13.58 (GND), U13.59 (GND), U13.60 (GND), U13.61 (GND), U13.62 (GND), U13.63 (GND), U13.64 (GND), U13.65 (GND); also elsewhere on the board
Reset: U13.31 (IO23); also elsewhere on the board
SWCLK: R86.2; also elsewhere on the board
SWDIO: U13.16 (IO0); also elsewhere on the board

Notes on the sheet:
ESP32-C5-MINI-1-N4 and its 3V3_D decoupling
Reset and download: EN RC delay, GPIO28 pull-up, flashing pads J2
Links to the MCU: SWCLK, SPI2 (UART4 fallback), ESP_CSn pull-up
USB pads J3: the USB Serial/JTAG controller (GPIO13 D-, GPIO14 D+)
Sheet ports

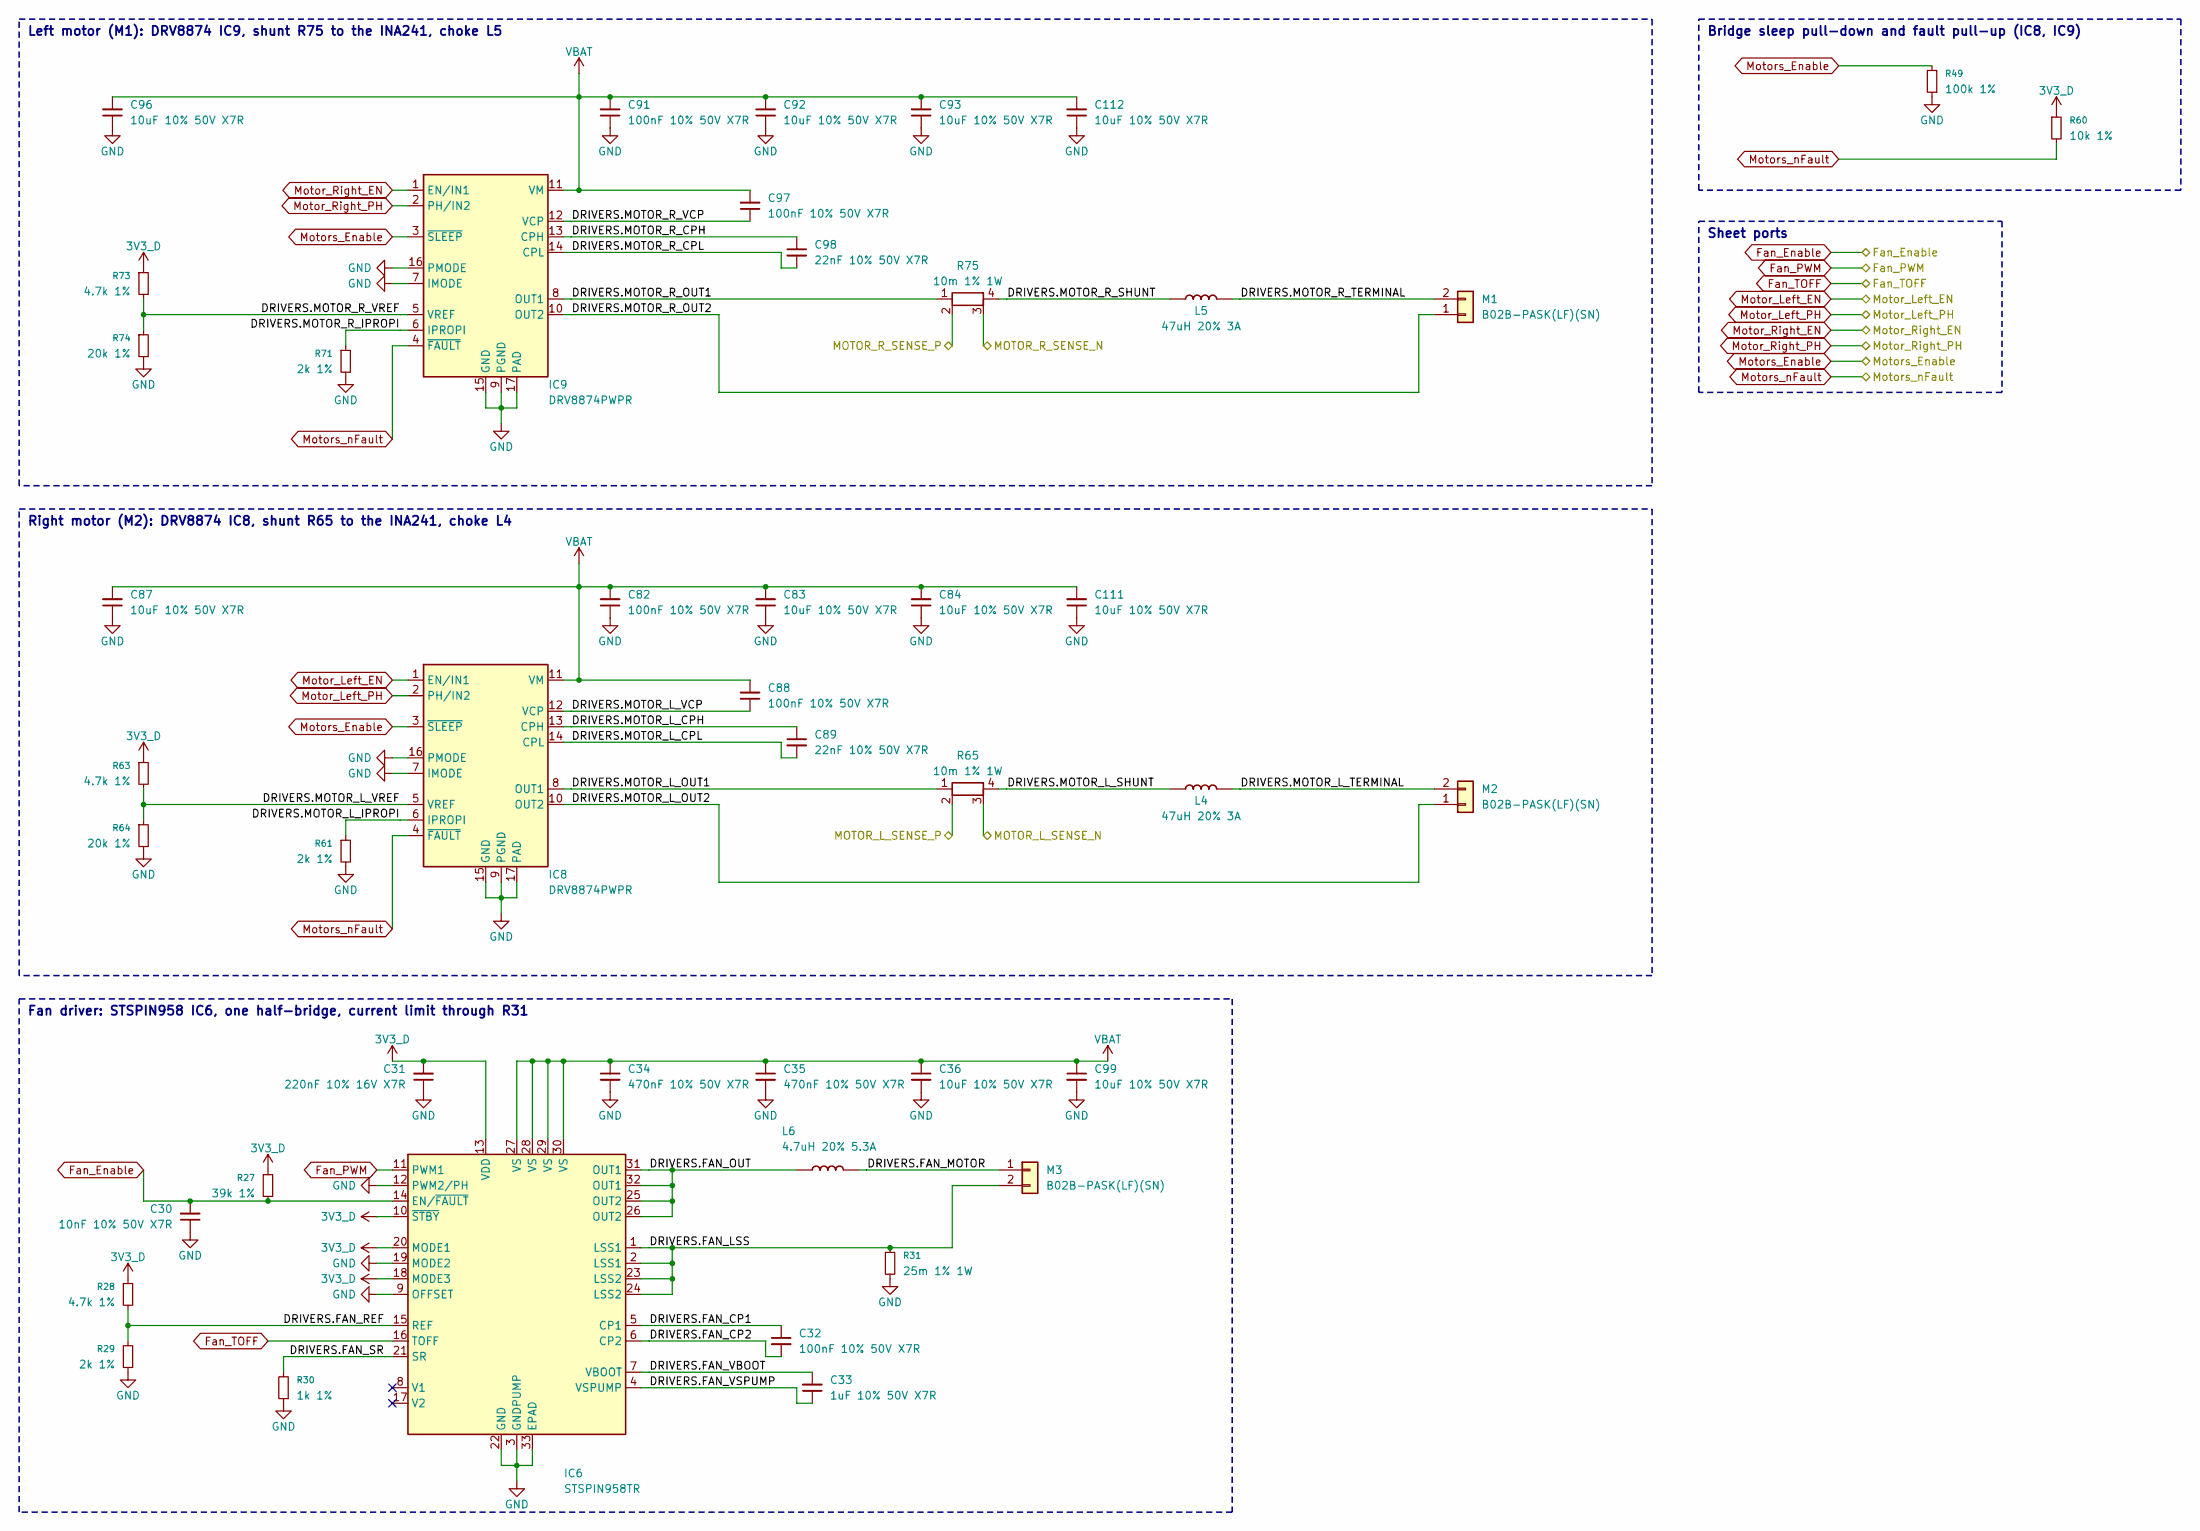
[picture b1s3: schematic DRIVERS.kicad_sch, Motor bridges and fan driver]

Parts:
C30: 10nF 10% 50V X7R; C_0402_1005Metric
C31: 220nF 10% 16V X7R; C_0402_1005Metric
C32, C82, C88, C91, C97: 100nF 10% 50V X7R; C_0402_1005Metric
C33: 1uF 10% 50V X7R; C_0805_2012Metric
C34, C35: 470nF 10% 50V X7R; C_0805_2012Metric
C36, C83, C84, C87, C92, C93, C96, C99, C111, C112: 10uF 10% 50V X7R; C_1210_3225Metric
C89, C98: 22nF 10% 50V X7R; C_0402_1005Metric
IC6: STSPIN958TR; QFN50P500X500X100-33N-D_SplitPaste
IC8, IC9: DRV8874PWPR; Texas_PWP0016J_HTSSOP-16-1EP_4.4x5mm_P0.65mm_EP3.4x5mm_Mask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
L4, L5: 47uH 20% 3A; L_MetalLions_MTQH707050S
L6: 4.7uH 20% 5.3A; L_MPS_MPL-AL5030
M1, M2, M3: B02B-PASK(LF)(SN); JST_PA_B02B-PASK_1x02_P2.00mm_Vertical
R27: 39k 1%; R_0402_1005Metric
R28, R63, R73: 4.7k 1%; R_0402_1005Metric
R29, R61, R71: 2k 1%; R_0402_1005Metric
R30: 1k 1%; R_0402_1005Metric
R31: 25m 1% 1W; R_1206_3216Metric
R49: 100k 1%; R_0402_1005Metric
R60: 10k 1%; R_0402_1005Metric
R64, R74: 20k 1%; R_0402_1005Metric
R65, R75: 10m 1% 1W; Vishay_WSK2512_6332Metric_5mR-200mR

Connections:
3V3_D: C31.2, IC6.10 (~STBY), IC6.13 (VDD), IC6.18 (MODE3), IC6.20 (MODE1), R27.1, R28.1, R60.1, R63.1, R73.1; also elsewhere on the board
DRIVERS.FAN_CP1: C32.1, IC6.5 (CP1)
DRIVERS.FAN_CP2: C32.2, IC6.6 (CP2)
DRIVERS.FAN_LSS: IC6.1 (LSS1), IC6.2 (LSS1), IC6.23 (LSS2), IC6.24 (LSS2), M3.2, R31.1
DRIVERS.FAN_MOTOR: L6.2, M3.1
DRIVERS.FAN_OUT: IC6.25 (OUT2), IC6.26 (OUT2), IC6.31 (OUT1), IC6.32 (OUT1), L6.1
DRIVERS.FAN_REF: IC6.15 (REF), R28.2, R29.2
DRIVERS.FAN_SR: IC6.21 (SR), R30.2
DRIVERS.FAN_VBOOT: C33.2, IC6.7 (VBOOT)
DRIVERS.FAN_VSPUMP: C33.1, IC6.4 (VSPUMP)
DRIVERS.IC6.NC_STSPIN958_V1: IC6.8 (V1)
DRIVERS.IC6.NC_STSPIN958_V2: IC6.17 (V2)
DRIVERS.MOTOR_L_CPH: C89.1, IC8.13 (CPH)
DRIVERS.MOTOR_L_CPL: C89.2, IC8.14 (CPL)
DRIVERS.MOTOR_L_IPROPI: IC8.6 (IPROPI), R61.1
DRIVERS.MOTOR_L_OUT1: IC8.8 (OUT1), R65.1 (I1)
DRIVERS.MOTOR_L_OUT2: IC8.10 (OUT2), M2.1
DRIVERS.MOTOR_L_SHUNT: L4.1, R65.4 (I2)
DRIVERS.MOTOR_L_TERMINAL: L4.2, M2.2
DRIVERS.MOTOR_L_VCP: C88.1, IC8.12 (VCP)
DRIVERS.MOTOR_L_VREF: IC8.5 (VREF), R63.2, R64.1
DRIVERS.MOTOR_R_CPH: C98.1, IC9.13 (CPH)
DRIVERS.MOTOR_R_CPL: C98.2, IC9.14 (CPL)
DRIVERS.MOTOR_R_IPROPI: IC9.6 (IPROPI), R71.1
DRIVERS.MOTOR_R_OUT1: IC9.8 (OUT1), R75.1 (I1)
DRIVERS.MOTOR_R_OUT2: IC9.10 (OUT2), M1.1
DRIVERS.MOTOR_R_SHUNT: L5.1, R75.4 (I2)
DRIVERS.MOTOR_R_TERMINAL: L5.2, M1.2
DRIVERS.MOTOR_R_VCP: C97.1, IC9.12 (VCP)
DRIVERS.MOTOR_R_VREF: IC9.5 (VREF), R73.2, R74.1
Fan_Enable: C30.2, IC6.14 (EN/~FAULT), R27.2; also elsewhere on the board
Fan_PWM: IC6.11 (PWM1); also elsewhere on the board
Fan_TOFF: IC6.16 (TOFF); also elsewhere on the board
GND: C30.1, C31.1, C34.2, C35.2, C36.2, C82.1, C83.1, C84.1, C87.1, C91.1, C92.1, C93.1, C96.1, C99.2, C111.1, C112.1, IC6.3 (GNDPUMP), IC6.9 (OFFSET), IC6.12 (PWM2/PH), IC6.19 (MODE2), IC6.22 (GND), IC6.33 (EPAD), IC8.7 (IMODE), IC8.9 (PGND), IC8.15 (GND), IC8.16 (PMODE), IC8.17 (PAD), IC9.7 (IMODE), IC9.9 (PGND), IC9.15 (GND), IC9.16 (PMODE), IC9.17 (PAD), R29.1, R30.1, R31.2, R49.1, R61.2, R64.2, R71.2, R74.2; also elsewhere on the board
Motor_L_Sense+: R65.2 (E1); also elsewhere on the board
Motor_L_Sense-: R65.3 (E2); also elsewhere on the board
Motor_Left_EN: IC8.1 (EN/IN1); also elsewhere on the board
Motor_Left_PH: IC8.2 (PH/IN2); also elsewhere on the board
Motor_R_Sense+: R75.2 (E1); also elsewhere on the board
Motor_R_Sense-: R75.3 (E2); also elsewhere on the board
Motor_Right_EN: IC9.1 (EN/IN1); also elsewhere on the board
Motor_Right_PH: IC9.2 (PH/IN2); also elsewhere on the board
Motors_Enable: IC8.3 (~SLEEP), IC9.3 (~SLEEP), R49.2; also elsewhere on the board
Motors_nFault: IC8.4 (~FAULT), IC9.4 (~FAULT), R60.2; also elsewhere on the board
VBAT: C34.1, C35.1, C36.1, C82.2, C83.2, C84.2, C87.2, C88.2, C91.2, C92.2, C93.2, C96.2, C97.2, C99.1, C111.2, C112.2, IC6.27 (VS), IC6.28 (VS), IC6.29 (VS), IC6.30 (VS), IC8.11 (VM), IC9.11 (VM); also elsewhere on the board

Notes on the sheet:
Left motor (M1): DRV8874 IC9, shunt R75 to the INA241, choke L5
Right motor (M2): DRV8874 IC8, shunt R65 to the INA241, choke L4
Fan driver: STSPIN958 IC6, one half-bridge, current limit through R31
Bridge sleep pull-down and fault pull-up (IC8, IC9)
Sheet ports
